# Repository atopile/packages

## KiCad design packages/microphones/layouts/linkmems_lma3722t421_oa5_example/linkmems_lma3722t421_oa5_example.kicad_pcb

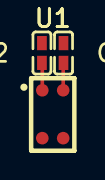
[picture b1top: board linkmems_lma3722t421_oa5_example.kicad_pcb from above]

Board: 2 copper layers, 3 parts (0 on the bottom side), 3 nets.

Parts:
C1: 10µF ±20% 6.3V X5R; C0402
C2: 100nF ±10% 16V X7R; C0402
U1: MIC-SMD_4P-L3.8-W2.3-P2.66-TL

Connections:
OUT: C1.2, U1.1
gnd: C2.2, U1.3, U1.4
hv: C2.1, U1.2

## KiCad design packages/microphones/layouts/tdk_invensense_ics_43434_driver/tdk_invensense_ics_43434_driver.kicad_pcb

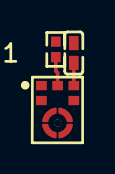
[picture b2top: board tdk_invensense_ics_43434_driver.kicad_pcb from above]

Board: 2 copper layers, 3 parts (0 on the bottom side), 3 nets.

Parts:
C1: 100nF ±10% 16V X7R; C0402
R1: 100kΩ ±1% 62.5mW; R0402
U1: MIC-SMD_6P-L3.5-W2.7-P0.90-BL

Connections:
SD: R1.1, U1.6
VDD: C1.1, U1.5
gnd: C1.2, R1.2, U1.3
